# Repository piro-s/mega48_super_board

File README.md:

## mega48_super_board  
Development board for Atmega48 developed by me and [mostovsky](https://github.com/mostovsky).  
Description for version v0.1 go to [this](docs/mega48_super_board_v0.1.md).  
Description for version v0.2 (some errors) go to [this](docs/mega48_super_board_v0.2.md).  

---
Version 0.3:  
1. Power supply from 7V to 15V or just 5V.  
2. Reverse polarity protection.  
3. There are separate connectors for external power, 5V, 3.3V and ground.  
4. Separate connectors for each pin of the MCU (except reset, xtal and power), compatible with prototyping board.  
5. External quartz at 8 MHz.  
6. Programming via USBasp.  
7. LED to indicate power and reset.  

Board size: 23x71 mm.  
Version 0.3 is the corrected version 0.2.  

---
#### scheme:  
scheme_v0.1:  
[pdf](docs/scheme_v0.1.pdf)  
scheme_v0.3:  
[pdf](docs/scheme_v0.3.pdf)  

---
#### helper:  
helper_v0.1:  
  
helper_v0.3 (also v0.2):  

---
#### pcb:  
##### pcb_v0.1:  
top screen:  
  
bottom_screen:  
  
##### pcb_v0.3:  
top screen:  
  
bottom_screen:  

---
#### work:  
  
AVRdude:  

---
#### gerber:  
Archive for production:  
[gerber_v0.1](https://github.com/piro-s/mega48_super_board/raw/main/gerber/mega48_super_board_v0.1.zip)  
[gerber_v0.3](https://github.com/piro-s/mega48_super_board/raw/main/gerber/mega48_super_board_v0.3.zip)

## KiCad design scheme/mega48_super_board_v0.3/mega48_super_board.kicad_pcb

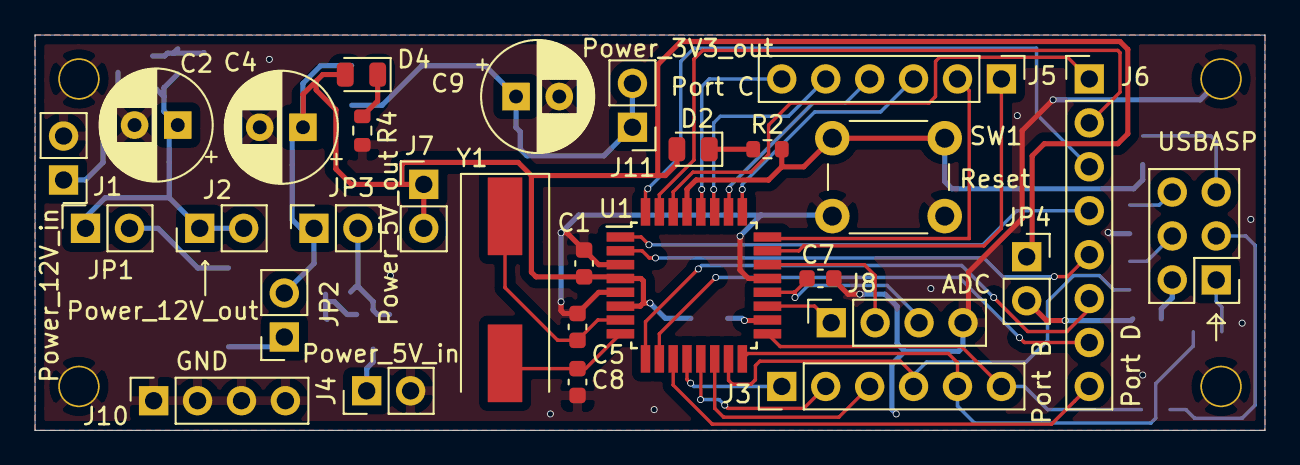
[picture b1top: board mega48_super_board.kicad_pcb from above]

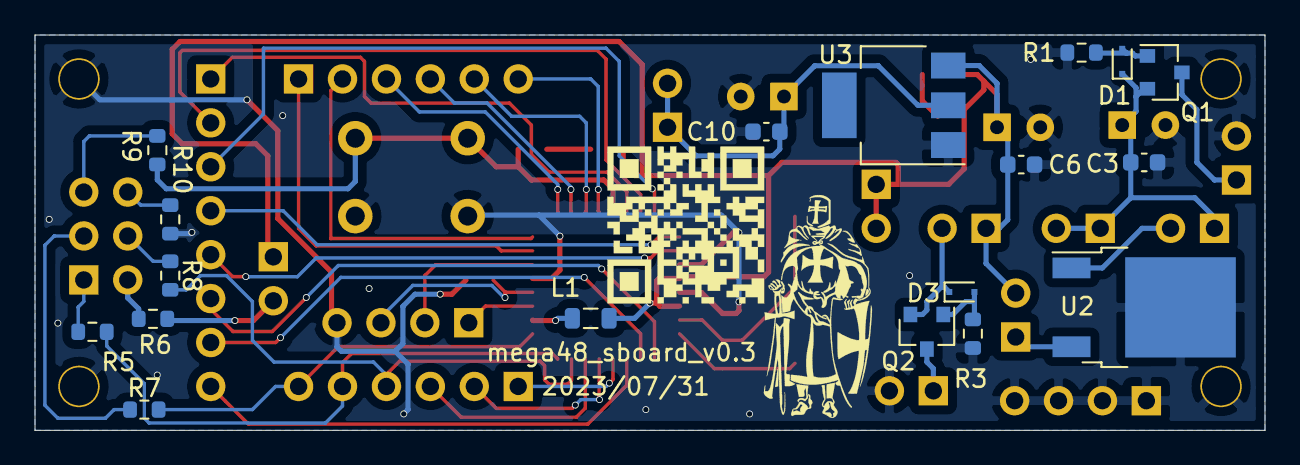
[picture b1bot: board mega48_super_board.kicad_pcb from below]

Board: 2 copper layers, 71.1 x 22.9 mm, 47 parts (18 on the bottom side), 47 nets.

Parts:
C1, C3, C6, C7, C10: 100n; C_0603_1608Metric
C2, C4, C9: 220u; CP_Radial_D6.3mm_P2.50mm
C5, C8: 22p; C_0603_1608Metric
D1, D3: BZX84Cxx; D_SC-80
D2, D4: LED; D_0805_2012Metric
J1: Power_12V_in; PinHeader_1x02_P2.54mm_Vertical
J2: Power_12V_out; PinHeader_1x02_P2.54mm_Vertical
J3: Port B; PinHeader_1x06_P2.54mm_Vertical
J4: Power_5V_in; PinHeader_1x02_P2.54mm_Vertical
J5: Port C; PinHeader_1x06_P2.54mm_Vertical
J6: Port D; PinHeader_1x08_P2.54mm_Vertical
J7: Power_5V_out; PinHeader_1x02_P2.54mm_Vertical
J8: ADC; PinSocket_1x04_P2.54mm_Vertical
J9: USBASP; PinHeader_2x03_P2.54mm_Vertical
J10: GND; PinSocket_1x04_P2.54mm_Vertical
J11: Power_3V3_out; PinHeader_1x02_P2.54mm_Vertical
JP1, JP2, JP3, JP4: Jumper_NO_Small; PinSocket_1x02_P2.54mm_Vertical
L1: 10u; L_0805_2012Metric
Q1, Q2: AO3401A; SOT-23
R1, R3: 10k; R_0603_1608Metric
R2, R4: 3k3; R_0603_1608Metric
R5, R7, R8, R9: 10R; R_0603_1608Metric
R6, R10: 1R8; R_0603_1608Metric
SW1: Reset; SW_PUSH_6mm
U1: ATmega48-20AU; TQFP-32_7x7mm_P0.8mm
U2: LM78M05_DPAK; TO-252-2
U3: AZ1117-3.3; SOT-223
Y1: HC49; Crystal_SMD_HC49-SD

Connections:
+5V: C1.1, C4.1, C6.1, D2.2, D4.2, J7.1, J7.2, JP2.2, JP3.1, JP4.1, L1.1, U1.4, U1.6, U3.3
/ADC6: J8.1, U1.19
/ADC7: J8.2, U1.22
/AREF: C7.1, J8.3, U1.20
/MISO: J3.5, R5.2, U1.16
/MOSI: J3.4, R8.2, U1.15
/PB0: J3.1, U1.12
/PB1: J3.2, U1.13
/PB2: J3.3, U1.14
/PC0: J5.1, U1.23
/PC1: J5.2, U1.24
/PC2: J5.3, U1.25
/PC3: J5.4, U1.26
/PC4: J5.5, U1.27
/PC5: J5.6, U1.28
/PD0: J6.1, U1.30
/PD1: J6.2, U1.31
/PD2: J6.3, U1.32
/PD3: J6.4, U1.1
/PD4: J6.5, U1.2
/PD5: J6.6, U1.9
/PD6: J6.7, U1.10
/PD7: J6.8, U1.11
/RESET: R2.2, R9.2, SW1.1, U1.29
/SCK: J3.6, R7.2, U1.17
/XTAL1: C5.1, U1.7, Y1.1
/XTAL2: C8.1, U1.8, Y1.2
GND: C1.2, C2.2, C3.2, C4.2, C5.2, C6.2, C7.2, C8.2, C9.2, C10.2, J1.2, J4.2, J8.4, J10.1, J10.2, J10.3, J10.4, R1.2, R3.2, R4.2, R10.2, SW1.2, U1.3, U1.5, U1.21, U2.2, U3.1
unnamed: C2.1, C3.1, D1.1, J2.1, J2.2, JP1.1, Q1.2
unnamed: C9.1, C10.1, J11.1, J11.2, U3.2
unnamed: D1.2, Q1.1, R1.1
unnamed: D2.1, R2.1
unnamed: D3.1, JP3.2, Q2.2
unnamed: D3.2, Q2.1, R3.1
unnamed: D4.1, R4.1
unnamed: J1.1, Q1.3
unnamed: J4.1, Q2.3
unnamed: J9.1, R5.1
unnamed: J9.2, R6.1
unnamed: J9.3, R7.1
unnamed: J9.4, R8.1
unnamed: J9.5, R9.1
unnamed: J9.6, R10.1
unnamed: JP1.2, U2.1
unnamed: JP2.1, U2.3
unnamed: JP4.2, R6.2
unnamed: L1.2, U1.18

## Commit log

2021-06-06 Upload v0.1
2021-06-06 Fix readme.md
2021-08-18 Upload v0.2
2021-08-18 Fix gerber links
2022-10-18 docs: Add helper_v0.2 + change readme
    Add helper for version v0.2 and create separate readme for each version.
2023-05-30 fix: helper_v0.1, reverse PD7,PD10
    Corrected the designation of the pins of the connector PD7, PD10.
2023-08-24 fix: Version 0.3
    Fix errors made in v0.2:
    1. The connector for programming must be soldered
    on the bottom side so that you can start the
    USBasp programmer, or solder a new cable for the
    programmer yourself.
    2. Transistors Q1 and Q2 must be upside-down
